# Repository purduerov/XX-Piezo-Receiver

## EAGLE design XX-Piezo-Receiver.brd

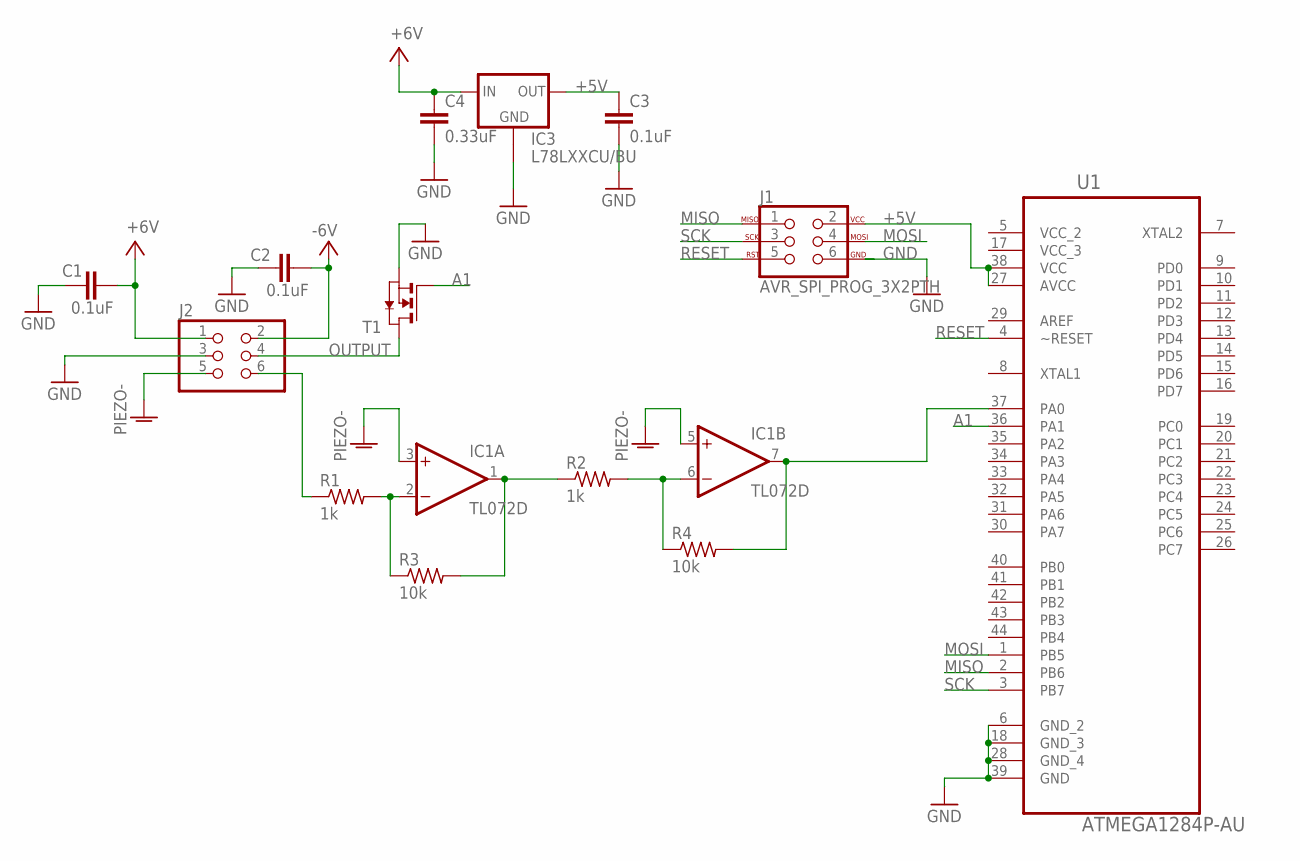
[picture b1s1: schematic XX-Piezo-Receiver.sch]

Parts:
C1, C2, C3: 0.1uF; C0603
C4: 0.33uF; C0603
IC1: TL072D; SO08
IC3: L78LXXCU/BU; SOT89
J1: AVR_SPI_PROG_3X2PTH; 2X3
J2: PINHD-2X3; 2X03
R1, R2: 1k; R0603
R3, R4: 10k; R0603
T1: NMOSSOT23; SOT-23
U1: ATMEGA1284P-AU; QFP80P1200X1200X120-44N

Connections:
+5V: C3.1, IC3.1 (OUT), J1.2, U1.27 (AVCC), U1.38 (VCC)
+6V: C1.2, C4.1, IC1.8 (V+), IC3.3 (IN), J2.1
-6V: C2.2, IC1.4 (V-), J2.2
A1: T1.3 (G), U1.36 (PA1)
GND: C1.1, C2.1, C3.2, C4.2, IC3.4 (GND1), J1.6, J2.3, T1.2 (S), U1.6 (GND_2), U1.18 (GND_3), U1.28 (GND_4), U1.39 (GND)
MISO: J1.1, U1.2 (PB6)
MOSI: J1.4, U1.1 (PB5)
OUT1: IC1.1 (OUT), R2.1, R3.2
OUT2: IC1.7 (OUT), R4.2, U1.37 (PA0)
OUTPUT: J2.4, T1.1 (D)
PIEZO+: J2.6, R1.1
PIEZO+1: IC1.2 (-IN), R1.2, R3.1
PIEZO+2: IC1.6 (-IN), R2.2, R4.1
PIEZO-: IC1.3 (+IN), IC1.5 (+IN), J2.5
RESET: J1.5, U1.4 (~RESET)
SCK: J1.3, U1.3 (PB7)
VCC_2: U1.5 (VCC_2)
VCC_3: U1.17 (VCC_3)

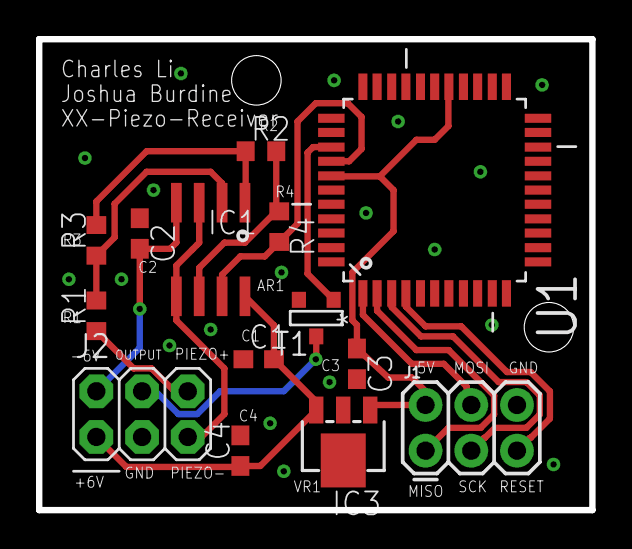
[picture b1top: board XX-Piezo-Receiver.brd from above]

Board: 2 copper layers, 30.7 x 26.2 mm, 14 parts (0 on the bottom side), 16 nets.

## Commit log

2018-03-19 Finished routing, first complete version
2018-03-19 Removed temp files
2018-03-19 Added gitignore
2018-03-20 Added MOSFET and removed uneccessary Op-Amp
2018-03-20 Nuke and start anew
2018-03-20 Cleaning
2018-03-20 Removed erroneious directories, op-amp. Added mosfet
2018-03-20 Added new gitignore
2018-03-22 Added correct mosfet, finished routing. No decoup caps yet.
2018-03-22 clean up, still learning git
2018-03-22 Added decoupling caps and mount hole.
2018-03-23 Change to 0603 components. Add new lin reg. Add new mount hole.
2018-03-23 Shifted everything 15 mil to the left.
2018-03-23 Moved components away from op-amp.

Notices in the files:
parts and their libraries:
SparkFun-Connectors: Licensing: Creative Commons ShareAlike 4.0 International - https://creativecommons.org/licenses/by-sa/4.0
